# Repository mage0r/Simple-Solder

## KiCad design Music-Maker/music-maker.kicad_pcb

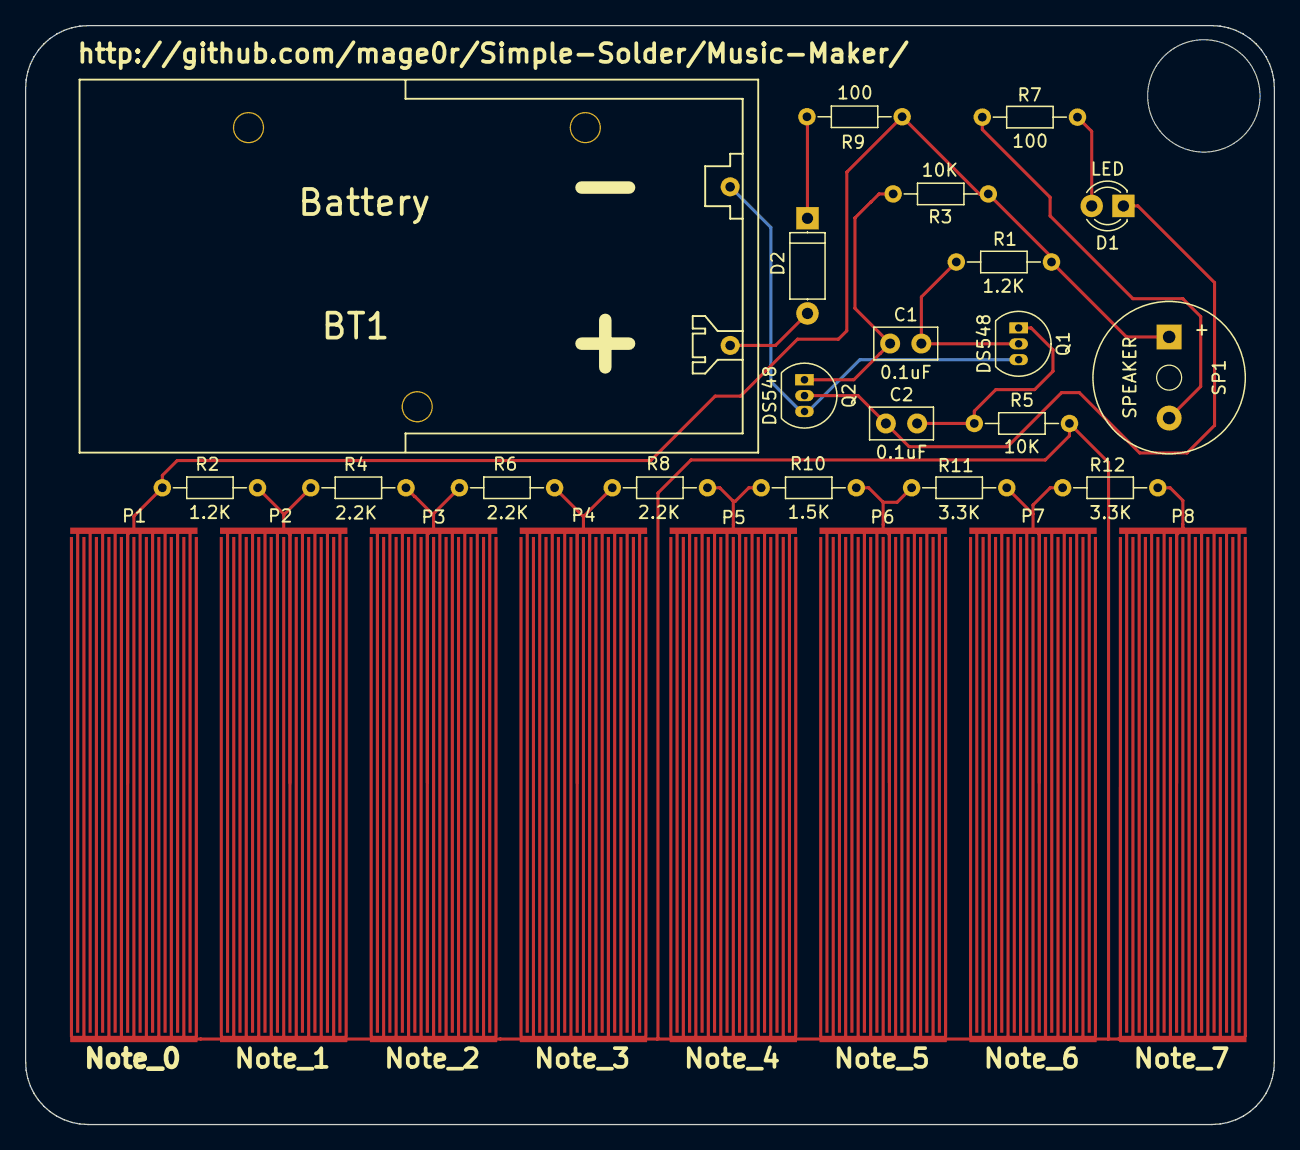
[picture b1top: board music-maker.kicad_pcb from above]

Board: 2 copper layers, 100.0 x 88.0 mm, 28 parts (0 on the bottom side), 18 nets.

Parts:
BT1: Battery; BH9VPC
C1, C2: 0.1uF; C_Disc_D5.0mm_W2.5mm_P2.50mm
D1: LED; LED_D3.0mm_FlatTop
D2: D; D_A-405_P7.62mm_Horizontal
P1: Note_0; piano_key
P2: Note_1; piano_key
P3: Note_2; piano_key
P4: Note_3; piano_key
P5: Note_4; piano_key
P6: Note_5; piano_key
P7: Note_6; piano_key
P8: Note_7; piano_key
Q1, Q2: DS548; TO-92_Inline_Narrow_Oval
R1, R2: 1.2K; R_Axial_DIN0204_L3.6mm_D1.6mm_P7.62mm_Horizontal
R3, R5: 10K; R_Axial_DIN0204_L3.6mm_D1.6mm_P7.62mm_Horizontal
R4, R6, R8: 2.2K; R_Axial_DIN0204_L3.6mm_D1.6mm_P7.62mm_Horizontal
R7, R9: 100; R_Axial_DIN0204_L3.6mm_D1.6mm_P7.62mm_Horizontal
R10: 1.5K; R_Axial_DIN0204_L3.6mm_D1.6mm_P7.62mm_Horizontal
R11, R12: 3.3K; R_Axial_DIN0204_L3.6mm_D1.6mm_P7.62mm_Horizontal
SP1: SPEAKER; piezo

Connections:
+9V: BT1.1, D2.2
/Notes: P1.2, R1.2, R2.2, R3.2, R9.2, SP1.1
/base: P1.1, P2.1, P3.1, P4.1, P5.1, P6.1, P7.1, P8.1, R5.2
GND: BT1.2, Q1.3, Q2.3
unnamed: C1.1, Q2.1, R3.1
unnamed: C1.2, Q1.2, R1.1
unnamed: C2.1, D1.1, Q2.2
unnamed: C2.2, Q1.1, R5.1
unnamed: D1.2, R7.1
unnamed: D2.1, R9.1
unnamed: P2.2, R2.1, R4.2
unnamed: P3.2, R4.1, R6.2
unnamed: P4.2, R6.1, R8.2
unnamed: P5.2, R8.1, R10.2
unnamed: P6.2, R10.1, R11.2
unnamed: P7.2, R11.1, R12.2
unnamed: P8.2, R12.1
unnamed: R7.2, SP1.2

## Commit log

2017-11-23 :lollipop: Added .gitattributes & .gitignore files
